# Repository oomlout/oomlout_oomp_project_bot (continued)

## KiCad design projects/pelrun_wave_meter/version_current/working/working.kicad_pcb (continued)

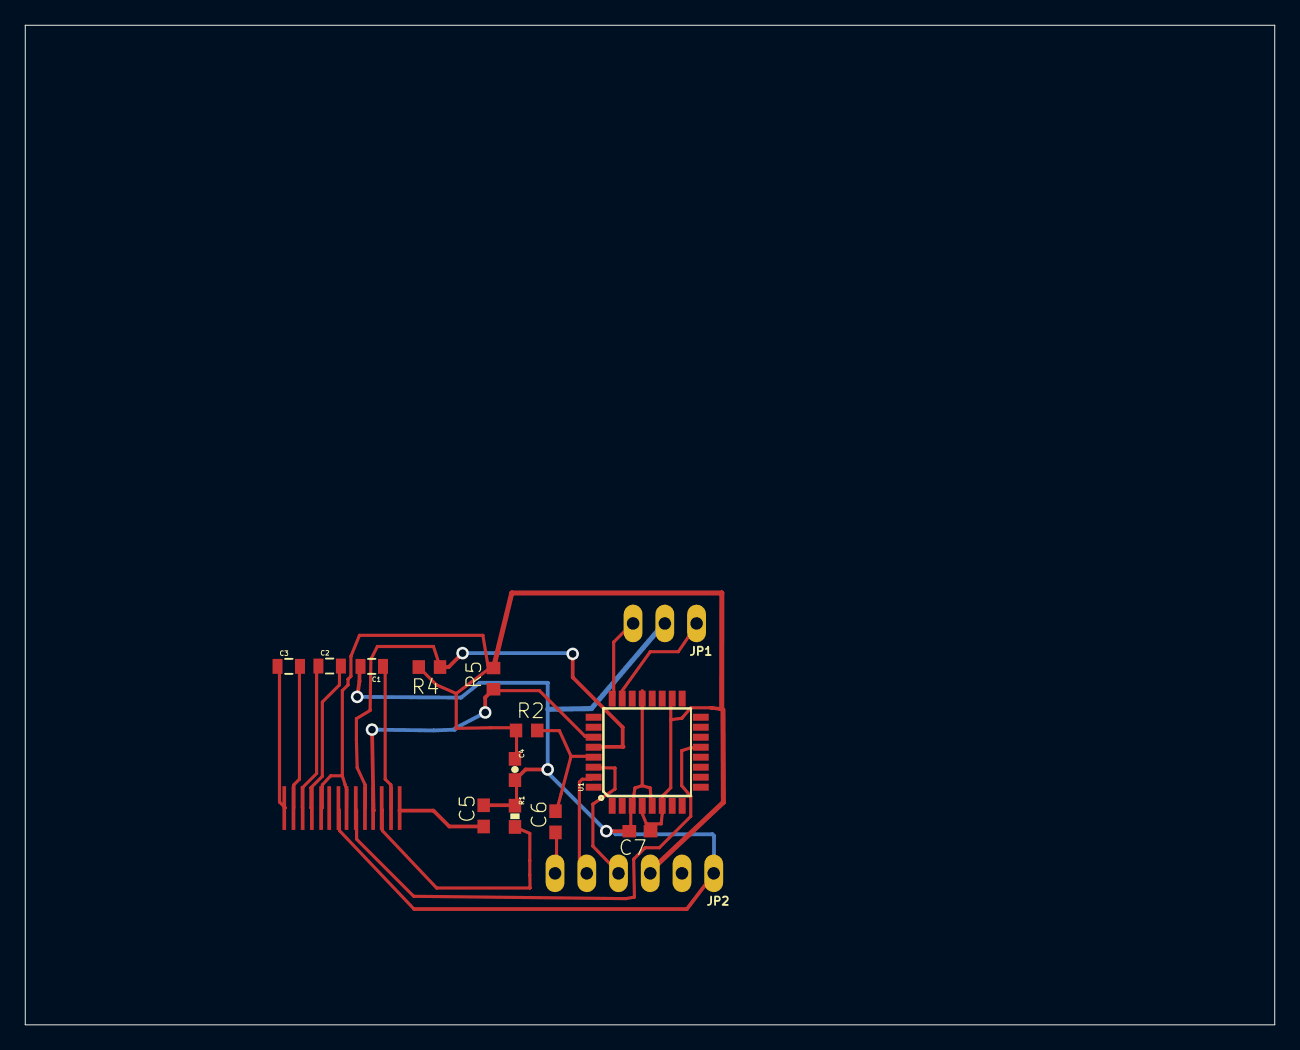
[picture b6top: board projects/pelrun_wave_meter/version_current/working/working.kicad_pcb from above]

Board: 2 copper layers, 100.0 x 80.0 mm, 15 parts (1 on the bottom side), 18 nets.

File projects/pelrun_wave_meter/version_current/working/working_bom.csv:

"Id";"Designator";"Footprint";"Quantity";"Designation";"Supplier and ref";
1;"U1";"TQFP32-08";1;"ATMEGA328P_TQFP";;;
2;"C5,C7,C6";"C0603";3;"";;;
3;"C3,C2";"0805";2;"1uF X5R";;;
4;"R1";"0603-RES";1;"390k";;;
5;"R5,R4,R2";"R0603";3;"";;;
6;"C4";"0603-CAP";1;"1uF";;;
7;"JP1";"1X03_OVAL";1;"";;;
8;"C1";"0805";1;"2.2uF";;;
9;"JP2";"1X06_OVAL";1;"";;;
10;"LCD1";"UG-9616GLBBG02_0.65MM_WRAPAROUND";1;"";;;

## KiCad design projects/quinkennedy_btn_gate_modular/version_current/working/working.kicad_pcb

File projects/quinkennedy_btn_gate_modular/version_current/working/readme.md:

# btn-gate-modular by quinkennedy  
This is a harvested standardized copy of a project from github.  
The original project can be found at:  
https://github.com/quinkennedy/btn-gate-modular  
Please consult that link for additional, details, files, and license information.  
Note: It was auto harvested and if the original repo had more than one board file or anything out of the ordinary the files here are likely not representative.

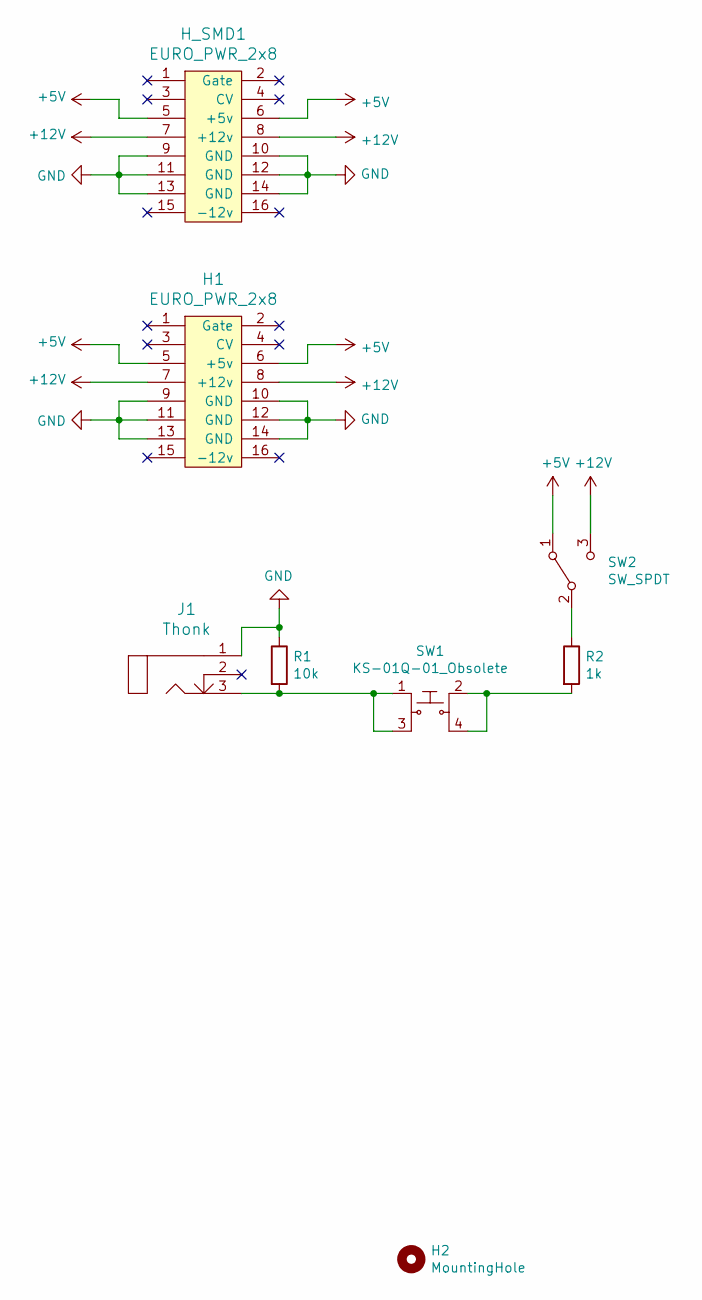
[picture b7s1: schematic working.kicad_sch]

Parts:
H1: EURO_PWR_2x8; PinHeader_2x08_P2.54mm_Vertical
H2: MountingHole; MountingHole_2.2mm_M2
H_SMD1: EURO_PWR_2x8; PinHeader_2x08_P2.54mm_Vertical_SMD
J1: Thonk; THONKICONN_mill
R1: 10k; Resistor_SMD+THTuniversal_0805to1206_RM10_HandSoldering
R2: 1k; Resistor_SMD+THTuniversal_0805to1206_RM10_HandSoldering
SW1: KS-01Q-01_Obsolete; PushButton_Round_D12mm_THT_KS-01Q-01; MPN KS-01Q-01; Digi-Key_PN EG4791-ND
SW2: SW_SPDT; Toggle_Switch_100SP1T1B4M2QE

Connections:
+5V: H1.5, H1.6 (+5v), H_SMD1.5, H_SMD1.6 (+5v), SW2.1 (A)
+12V: H1.7, H1.8 (+12v), H_SMD1.7, H_SMD1.8 (+12v), SW2.3 (C)
GND: H1.9, H1.10 (GND), H1.11, H1.12 (GND), H1.13, H1.14 (GND), H_SMD1.9, H_SMD1.10 (GND), H_SMD1.11, H_SMD1.12 (GND), H_SMD1.13, H_SMD1.14 (GND), J1.1, R1.1
unnamed: J1.3, R1.2, SW1.1, SW1.3
unnamed: R2.1, SW2.2 (B)
unnamed: R2.2, SW1.2, SW1.4

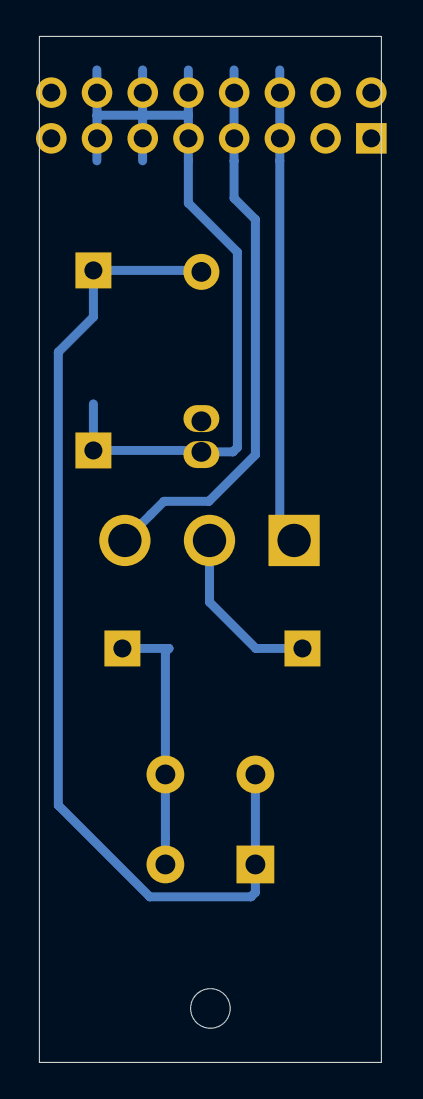
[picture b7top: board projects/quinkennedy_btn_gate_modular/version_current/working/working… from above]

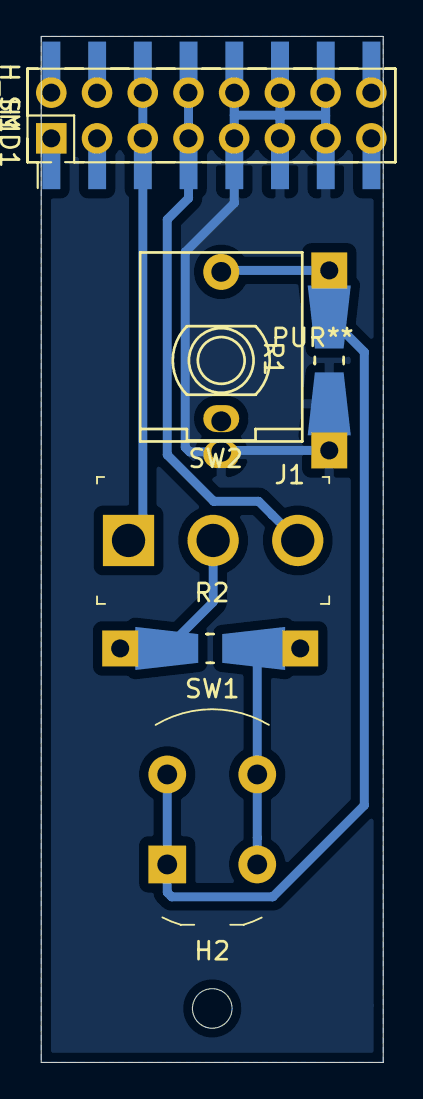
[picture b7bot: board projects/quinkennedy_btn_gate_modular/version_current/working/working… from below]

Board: 2 copper layers, 19.0 x 57.0 mm, 8 parts (8 on the bottom side), 6 nets.

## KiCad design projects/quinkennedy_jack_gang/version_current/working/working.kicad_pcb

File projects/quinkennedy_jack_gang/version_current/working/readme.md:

# jack-gang by quinkennedy  
This is a harvested standardized copy of a project from github.  
The original project can be found at:  
https://github.com/quinkennedy/jack-gang  
Please consult that link for additional, details, files, and license information.  
Note: It was auto harvested and if the original repo had more than one board file or anything out of the ordinary the files here are likely not representative.

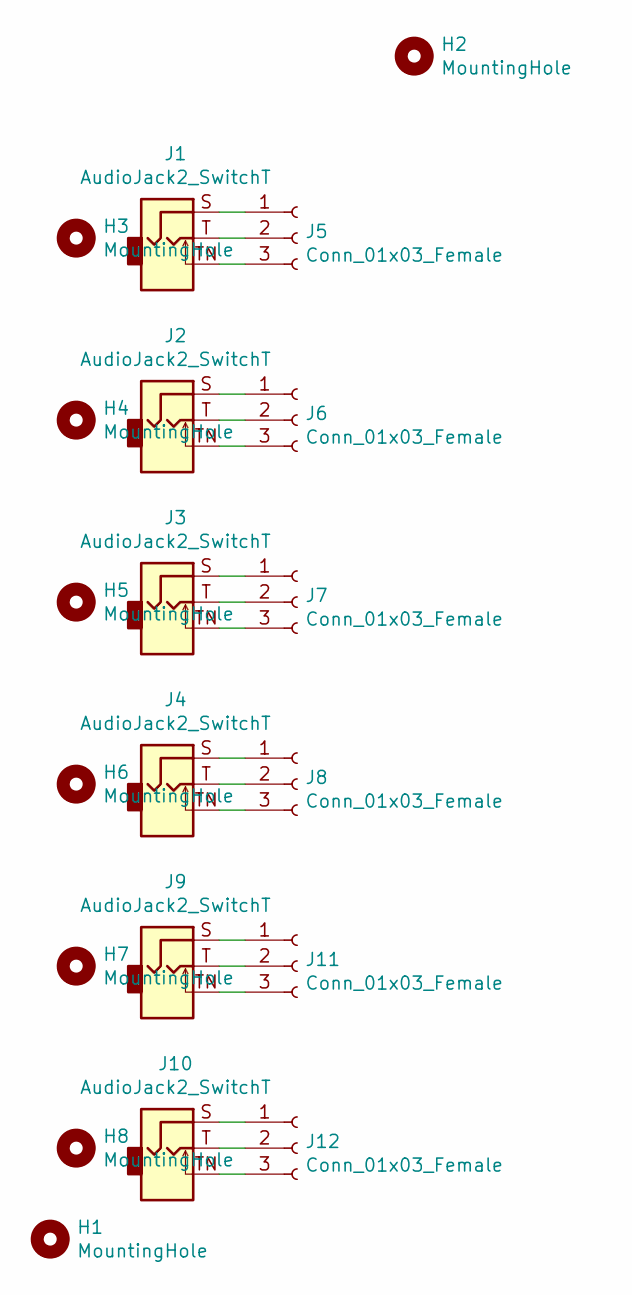
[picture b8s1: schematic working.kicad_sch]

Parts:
H1, H2: MountingHole; MountingHole_3.2mm_M3
H3, H4, H5, H6, H7, H8: MountingHole; jack_hole
J1, J2, J3, J4, J9, J10: AudioJack2_SwitchT; THONKICONN_mill_kicad
J5, J6, J7, J8, J11, J12: Conn_01x03_Female; PinHeader_1x03_P2.54mm_Vertical

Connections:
unnamed: J1.S, J5.1
unnamed: J1.T, J5.2
unnamed: J1.TN, J5.3
unnamed: J2.S, J6.1
unnamed: J2.T, J6.2
unnamed: J2.TN, J6.3
unnamed: J3.S, J7.1
unnamed: J3.T, J7.2
unnamed: J3.TN, J7.3
unnamed: J4.S, J8.1
unnamed: J4.T, J8.2
unnamed: J4.TN, J8.3
unnamed: J10.S, J12.1
unnamed: J10.T, J12.2
unnamed: J10.TN, J12.3
unnamed: J9.S, J11.1
unnamed: J9.T, J11.2
unnamed: J9.TN, J11.3

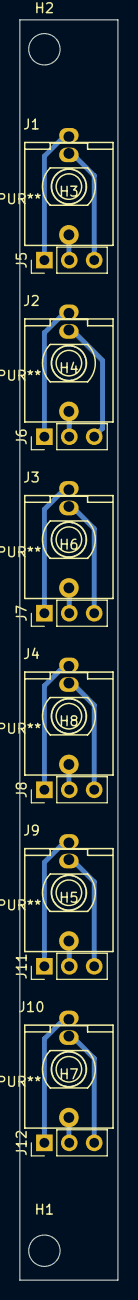
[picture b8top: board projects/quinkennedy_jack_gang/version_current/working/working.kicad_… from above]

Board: 2 copper layers, 10.0 x 128.5 mm, 20 parts (0 on the bottom side), 18 nets.

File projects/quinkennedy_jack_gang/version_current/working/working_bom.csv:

"Id";"Designator";"Footprint";"Quantity";"Designation";"Supplier and ref";
1;"J5,J6,J7,J8,J11,J12";"PinHeader_1x03_P2.54mm_Vertical";6;"Conn_01x03_Female";;;
2;"J1,J2,J3,J4,J9,J10";"THONKICONN_mill_kicad";6;"AudioJack2_SwitchT";;;
3;"H3,H4,H5,H6,H7,H8";"jack_hole";6;"MountingHole";;;
